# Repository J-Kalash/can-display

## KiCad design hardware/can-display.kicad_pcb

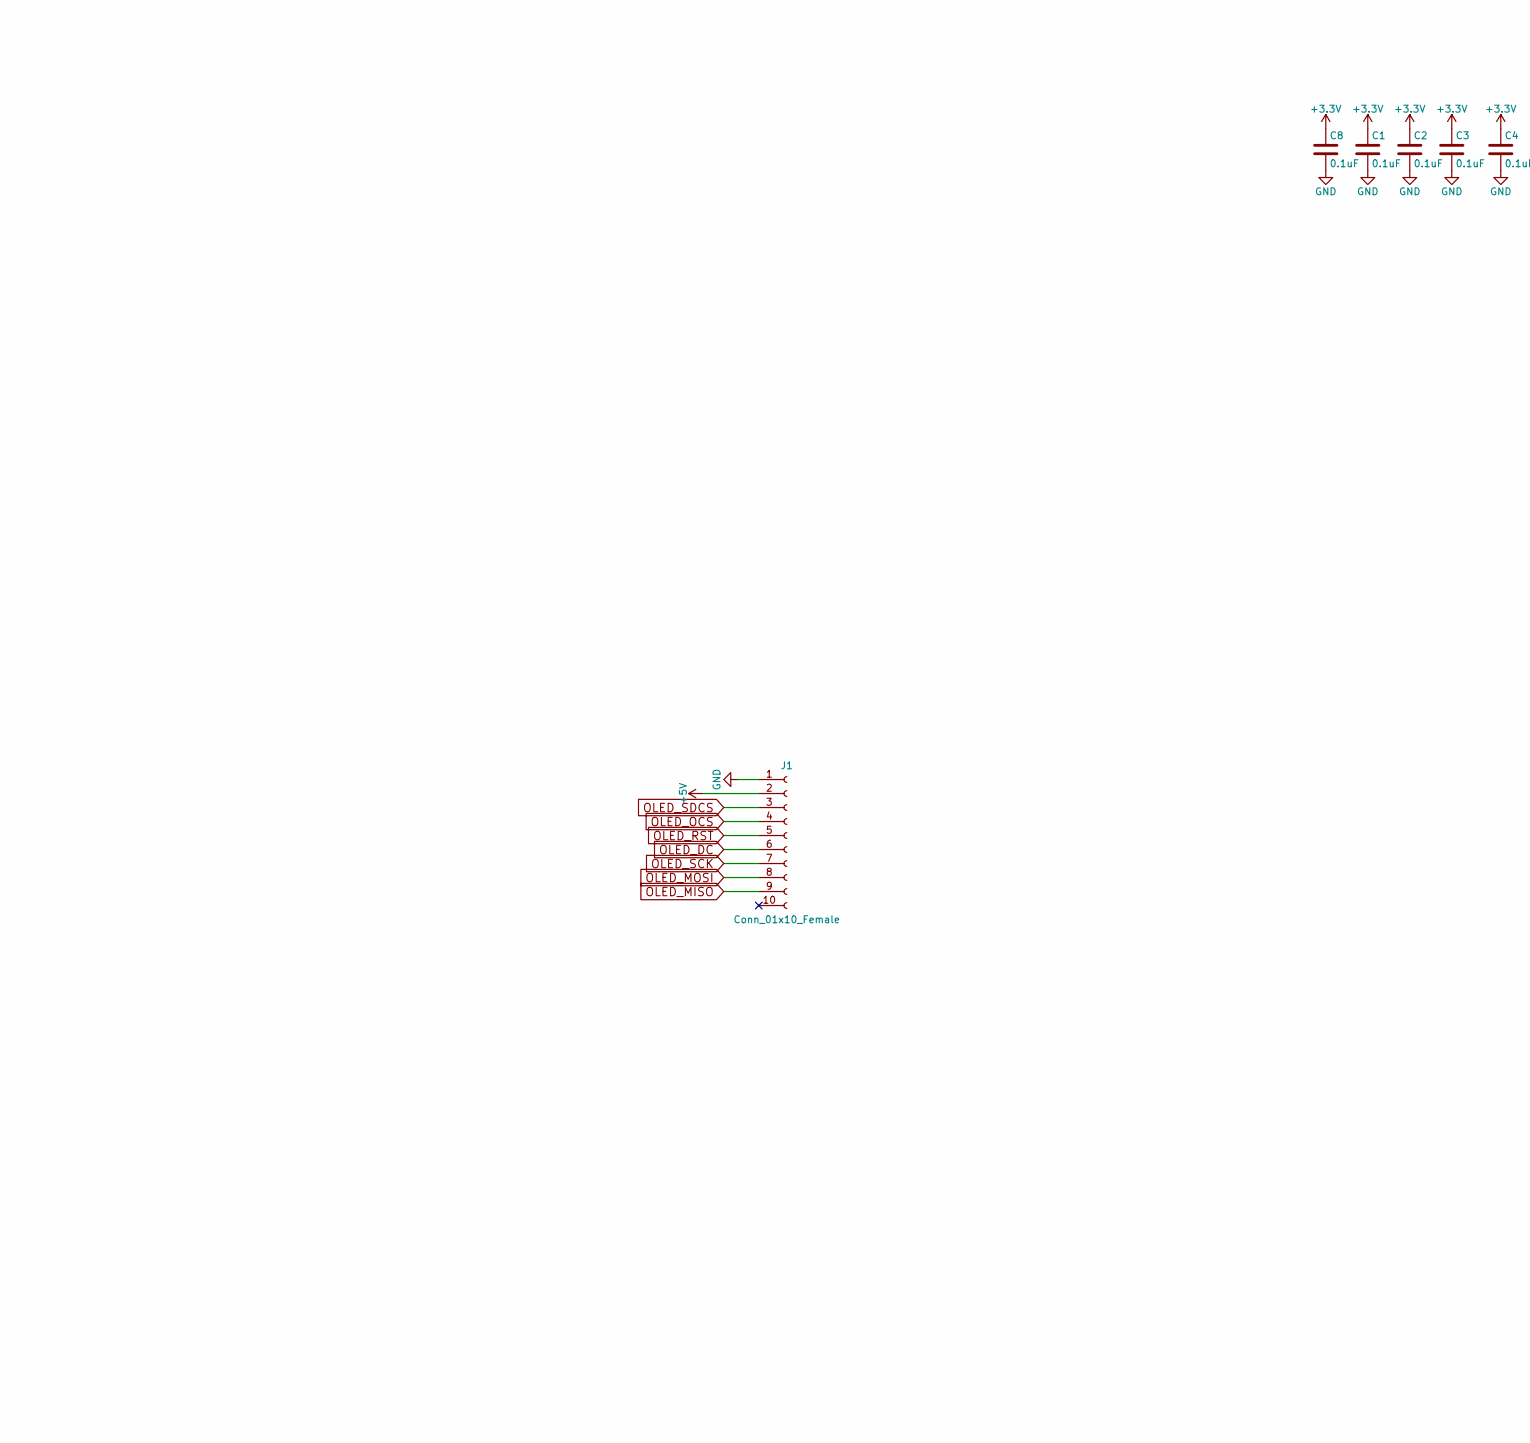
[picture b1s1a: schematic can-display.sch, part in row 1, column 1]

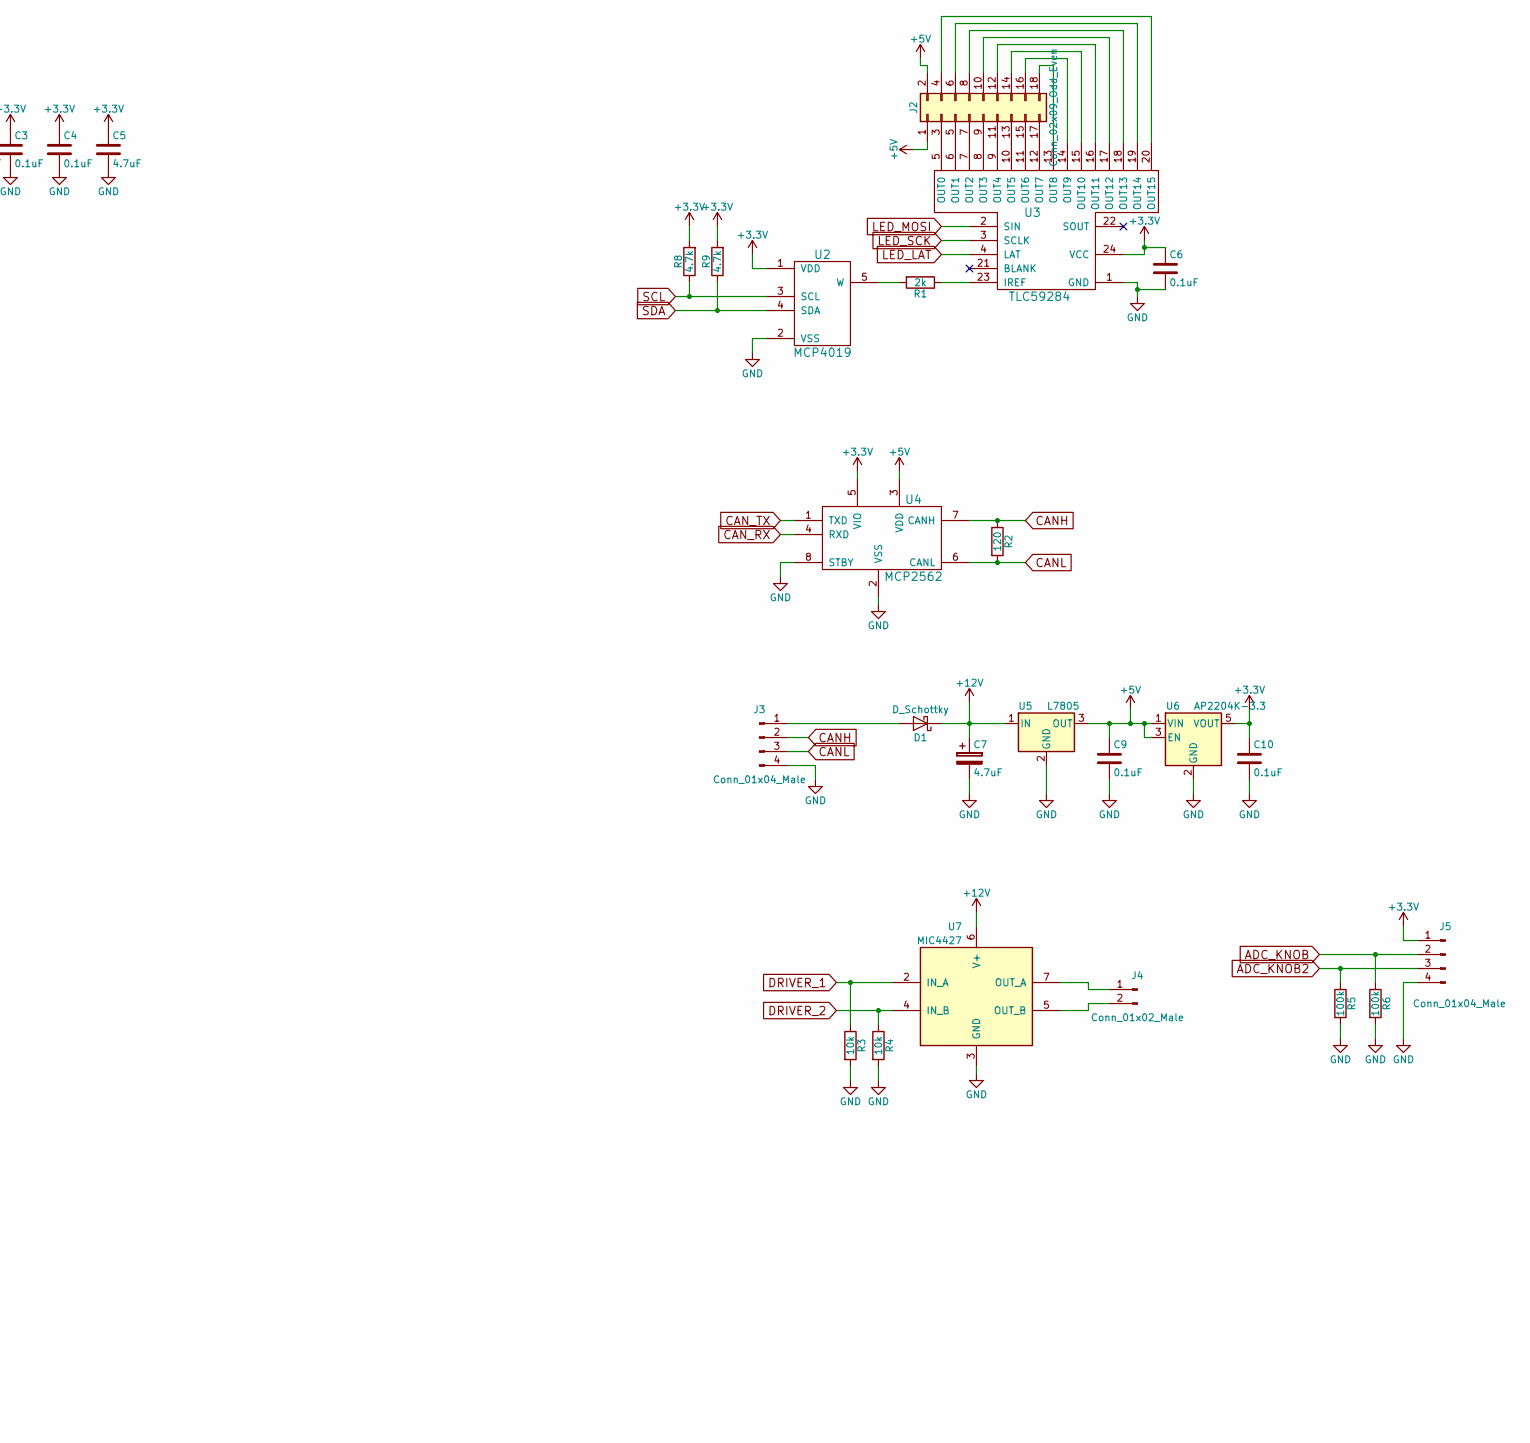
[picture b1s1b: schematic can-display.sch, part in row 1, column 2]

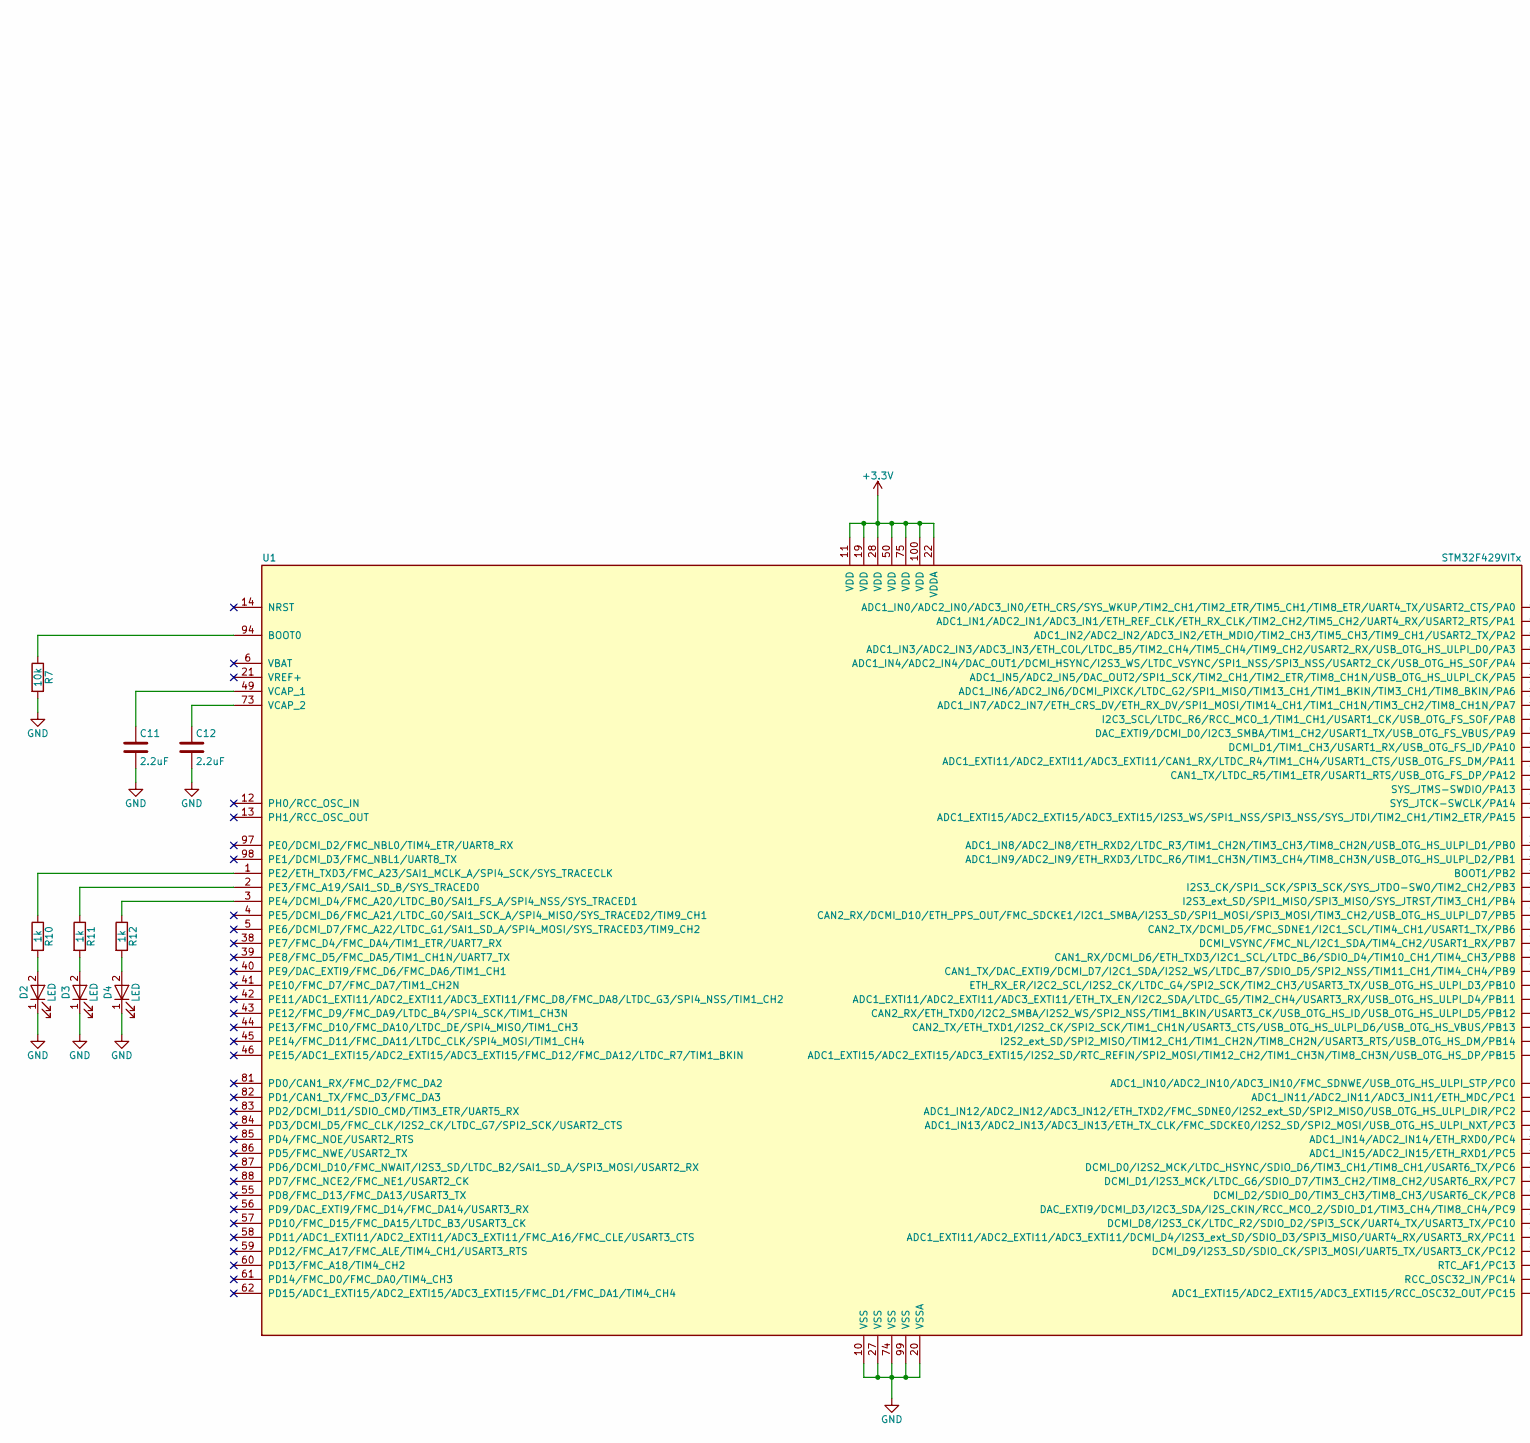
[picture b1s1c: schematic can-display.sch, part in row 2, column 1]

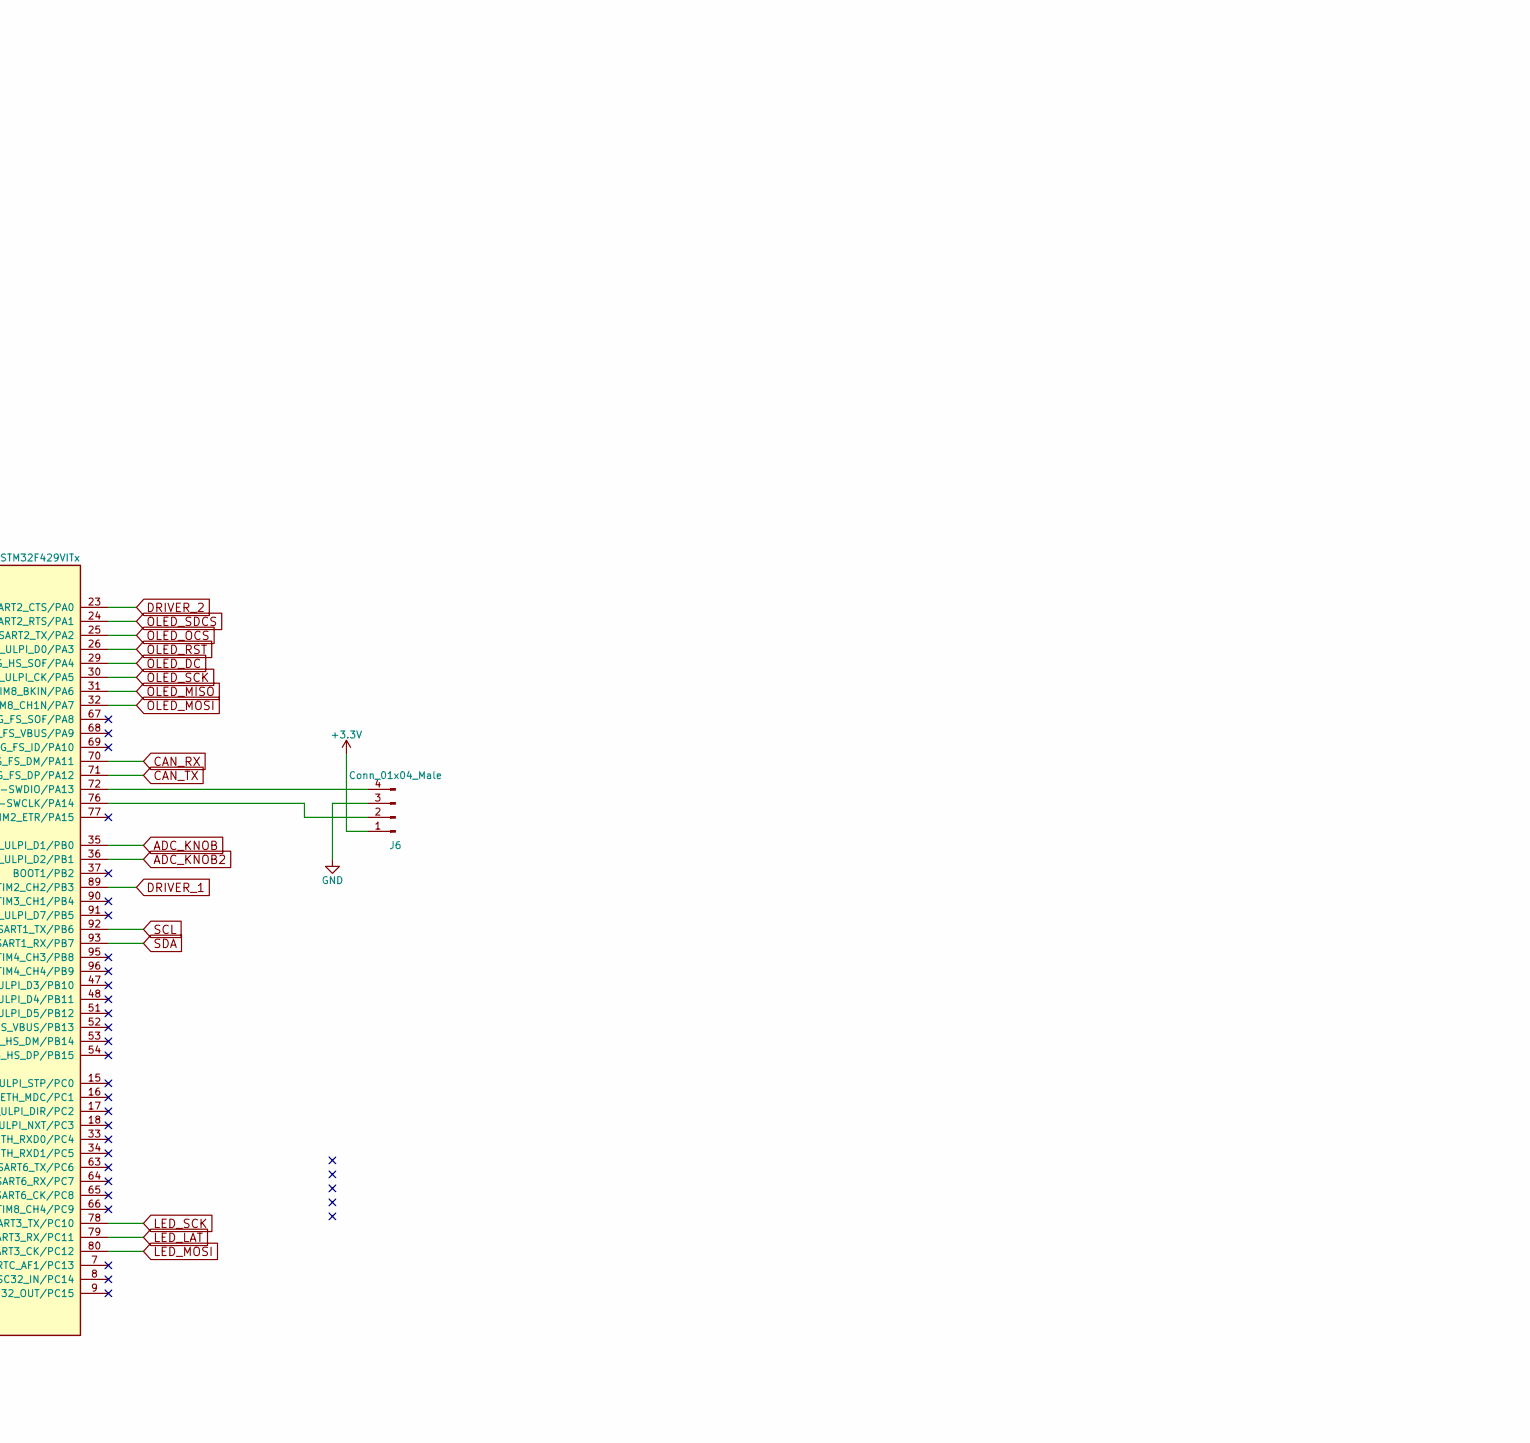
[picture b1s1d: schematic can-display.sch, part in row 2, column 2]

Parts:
C1, C2, C3, C4, C6, C8, C9, C10: 0.1uF; C_0603
C5: 4.7uF; C_0603
C7: 4.7uF; CP_Tantalum_Case-B_EIA-3528-21_Wave
C11, C12: 2.2uF; C_0603
D1: D_Schottky; D_SOD-123F
D2, D3, D4: LED; LED_0603_HandSoldering
J1: Conn_01x10_Female; Socket_Strip_Straight_1x10_Pitch2.54mm
J2: Conn_02x09_Odd_Even; Socket_Strip_Straight_2x09_Pitch2.54mm_SMD
J3, J5: Conn_01x04_Male; JST_XH_B04B-XH-A_04x2.50mm_Straight
J4: Conn_01x02_Male; JST_XH_B02B-XH-A_02x2.50mm_Straight
J6: Conn_01x04_Male; Pin_Header_Straight_1x04_Pitch2.54mm
R1: 2k; R_0603
R2: 120; R_0603
R3, R4, R7: 10k; R_0603
R5, R6: 100k; R_0603
R8, R9: 4.7k; R_0603
R10, R11, R12: 1k; R_0603
U1: STM32F429VITx; LQFP-100_14x14mm_Pitch0.5mm
U2: MCP4019; SOT-353_SC-70-5_Handsoldering
U3: TLC59284; SSOP-24_3.9x8.7mm_Pitch0.635mm
U4: MCP2562; SOIC-8_3.9x4.9mm_Pitch1.27mm
U5: L7805; TO-252-2
U6: AP2204K-3.3; SOT-23-5_HandSoldering
U7: MIC4427; SOIC-8_3.9x4.9mm_Pitch1.27mm

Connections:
+3V3: C1.1, C2.1, C3.1, C4.1, C5.1, C6.1, C8.1, C10.1, J5.1, J6.1, R8.2, R9.2, U1.11 (VDD), U1.19 (VDD), U1.22 (VDDA), U1.28 (VDD), U1.50 (VDD), U1.75 (VDD), U1.100 (VDD), U2.1 (VDD), U3.24 (VCC), U4.5 (VIO), U6.5 (VOUT)
+5V: C9.1, J1.2, J2.1, J2.2, U4.3 (VDD), U5.3 (OUT), U6.1 (VIN), U6.3 (EN)
+12V: C7.1, D1.1 (K), U5.1 (IN), U7.6 (V+)
ADC_KNOB: J5.2, R6.1, U1.35 (ADC1_IN8/ADC2_IN8/ETH_RXD2/LTDC_R3/TIM1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)
ADC_KNOB2: J5.3, R5.1, U1.36 (ADC1_IN9/ADC2_IN9/ETH_RXD3/LTDC_R6/TIM1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)
CANH: J3.2, R2.1, U4.7 (CANH)
CANL: J3.3, R2.2, U4.6 (CANL)
CAN_RX: U1.70 (ADC1_EXTI11/ADC2_EXTI11/ADC3_EXTI11/CAN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), U4.4 (RXD)
CAN_TX: U1.71 (CAN1_TX/LTDC_R5/TIM1_ETR/USART1_RTS/USB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), U4.1 (TXD)
DRIVER_1: R3.1, U1.89 (I2S3_CK/SPI1_SCK/SPI3_SCK/SYS_JTDO-SWO/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), U7.2 (IN_A)
DRIVER_2: R4.1, U1.23 (ADC1_IN0/ADC2_IN0/ADC3_IN0/ETH_CRS/SYS_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), U7.4 (IN_B)
GND: C1.2, C2.2, C3.2, C4.2, C5.2, C6.2, C7.2, C8.2, C9.2, C10.2, C11.2, C12.2, D2.1 (K), D3.1 (K), D4.1 (K), J1.1, J3.4, J5.4, J6.3, R3.2, R4.2, R5.2, R6.2, R7.2, U1.10 (VSS), U1.20 (VSSA), U1.27 (VSS), U1.74 (VSS), U1.99 (VSS), U2.2 (VSS), U3.1 (GND), U4.2 (VSS), U4.8 (STBY), U5.2 (GND), U6.2 (GND), U7.3 (GND)
LED_LAT: U1.79 (ADC1_EXTI11/ADC2_EXTI11/ADC3_EXTI11/DCM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), U3.4 (LAT)
LED_MOSI: U1.80 (DCMI_D9/I2S3_SD/SDIO_CK/SPI3_MOSI/UART5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), U3.2 (SIN)
LED_SCK: U1.78 (DCMI_D8/I2S3_CK/LTDC_R2/SDIO_D2/SPI3_SC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), U3.3 (SCLK)
unnamed: C11.1, U1.49 (VCAP_1)
unnamed: C12.1, U1.73 (VCAP_2)
unnamed: D1.2 (A), J3.1
unnamed: D2.2 (A), R10.2
unnamed: D3.2 (A), R11.2
unnamed: D4.2 (A), R12.2
unnamed: J2.3, U3.5 (OUT0)
unnamed: J2.4, U3.20 (OUT15)
unnamed: J2.5, U3.6 (OUT1)
unnamed: J2.6, U3.19 (OUT14)
unnamed: J2.7, U3.7 (OUT2)
unnamed: J2.8, U3.18 (OUT13)
unnamed: J2.9, U3.8 (OUT3)
unnamed: J2.10, U3.17 (OUT12)
unnamed: J2.11, U3.9 (OUT4)
unnamed: J2.12, U3.16 (OUT11)
unnamed: J2.13, U3.10 (OUT5)
unnamed: J2.14, U3.15 (OUT10)
unnamed: J2.15, U3.11 (OUT6)
unnamed: J2.16, U3.14 (OUT9)
unnamed: J2.17, U3.12 (OUT7)
unnamed: J2.18, U3.13 (OUT8)
unnamed: J4.1, U7.7 (OUT_A)
unnamed: J4.2, U7.5 (OUT_B)
unnamed: J6.2, U1.76 (SYS_JTCK-SWCLK/PA14)
unnamed: J6.4, U1.72 (SYS_JTMS-SWDIO/PA13)
unnamed: R1.1, U3.23 (IREF)
unnamed: R1.2, U2.5 (W)
unnamed: R7.1, U1.94 (BOOT0)
unnamed: R10.1, U1.1 (PE2/ETH_TXD3/FMC_A23/SAI1_MCLK_A/SPI4_S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)
unnamed: R11.1, U1.2 (PE3/FMC_A19/SAI1_SD_B/SYS_TRACED0)
unnamed: R12.1, U1.3 (PE4/DCMI_D4/FMC_A20/LTDC_B0/SAI1_FS_A/S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)
OLED_DC: J1.6, U1.29 (ADC1_IN4/ADC2_IN4/DAC_OUT1/DCMI_HSYNC/I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)
OLED_MISO: J1.9, U1.31 (ADC1_IN6/ADC2_IN6/DCMI_PIXCK/LTDC_G2/SP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)
OLED_MOSI: J1.8, U1.32 (ADC1_IN7/ADC2_IN7/ETH_CRS_DV/ETH_RX_DV/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)
OLED_OCS: J1.4, U1.25 (ADC1_IN2/ADC2_IN2/ADC3_IN2/ETH_MDIO/TIM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)
OLED_RST: J1.5, U1.26 (ADC1_IN3/ADC2_IN3/ADC3_IN3/ETH_COL/LTDC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)
OLED_SCK: J1.7, U1.30 (ADC1_IN5/ADC2_IN5/DAC_OUT2/SPI1_SCK/TIM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)
OLED_SDCS: J1.3, U1.24 (ADC1_IN1/ADC2_IN1/ADC3_IN1/ETH_REF_CLK/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)
SCL: R8.1, U1.92 (CAN2_TX/DCMI_D5/FMC_SDNE1/I2C1_SCL/TIM4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), U2.3 (SCL)
SDA: R9.1, U1.93 (DCMI_VSYNC/FMC_NL/I2C1_SDA/TIM4_CH2/USA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), U2.4 (SDA)

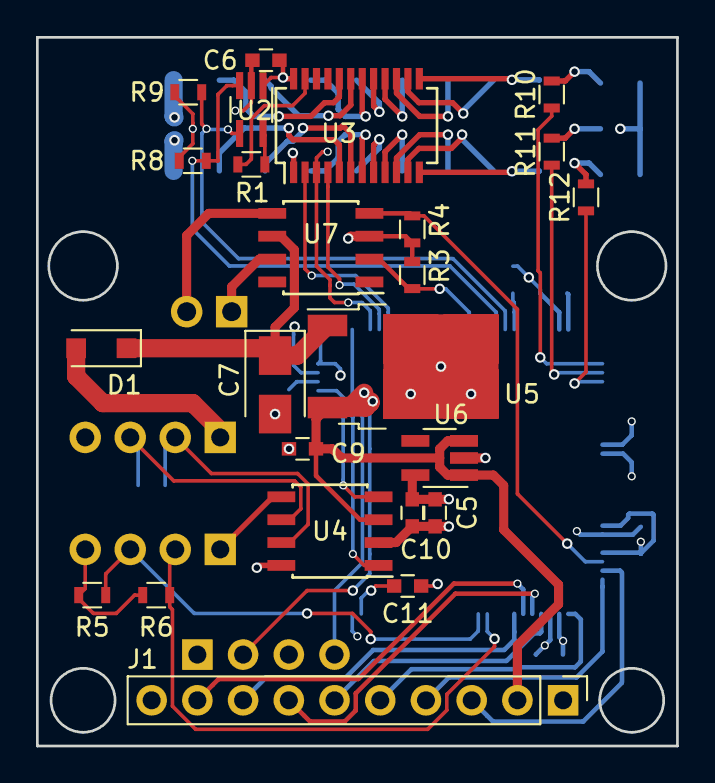
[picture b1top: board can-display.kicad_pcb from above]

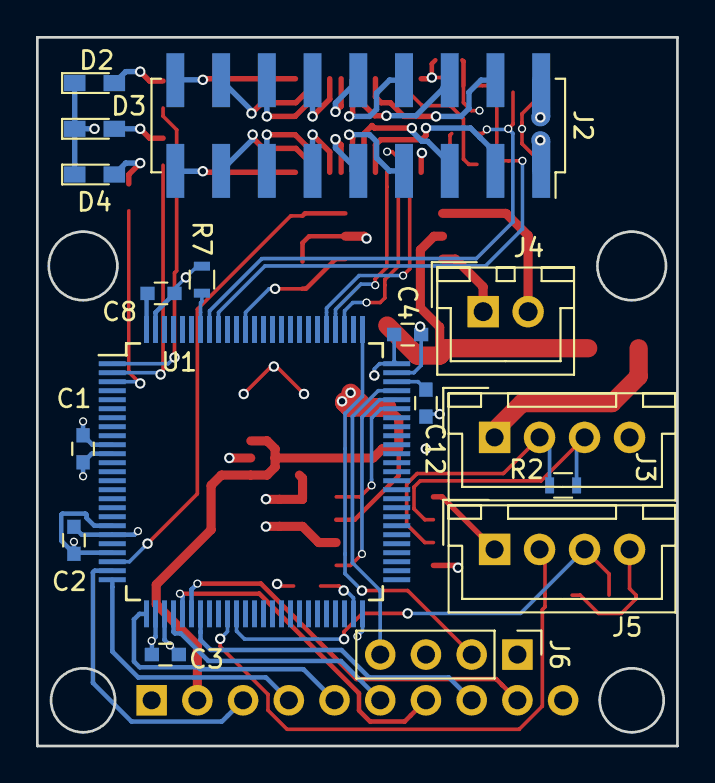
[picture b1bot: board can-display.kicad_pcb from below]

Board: 4 copper layers, 35.6 x 39.4 mm, 41 parts (17 on the bottom side), 56 nets.

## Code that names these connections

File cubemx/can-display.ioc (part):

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Mcu.Name=STM32F072C(8-B)Tx
Mcu.Package=LQFP48
Mcu.UserName=STM32F072C8Tx
PA1.Signal=GPIO_Output
PA11.Mode=Master
PA11.Signal=CAN_RX
PA12.Mode=Master
PA12.Signal=CAN_TX
PA2.Signal=GPIO_Output
PA3.Signal=GPIO_Output
PA4.Signal=GPIO_Output
PA5.Mode=Full_Duplex_Master
PA5.Signal=SPI1_SCK
PA6.Mode=Full_Duplex_Master
PA6.Signal=SPI1_MISO
PB0.Mode=IN8
PB0.Signal=ADC_IN8
PB1.Mode=IN9
PB1.Signal=ADC_IN9
PB12.Signal=GPIO_Output
PB13.Mode=TX_Only_Simplex_Unidirect_Master
PB13.Signal=SPI2_SCK
PB15.Mode=TX_Only_Simplex_Unidirect_Master
PB15.Signal=SPI2_MOSI
PB3.Signal=S_TIM2_CH2
PB4.Signal=S_TIM3_CH1
PB5.Mode=Full_Duplex_Master
PB5.Signal=SPI1_MOSI
PB6.Mode=I2C
PB6.Signal=I2C1_SCL
PB7.Mode=I2C
PB7.Signal=I2C1_SDA
RCC.SYSCLKFreq_VALUE=48000000
RCC.SYSCLKSource=RCC_SYSCLKSOURCE_HSI48

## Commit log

2018-04-01 gitignore
2018-04-01 gitignore again
2018-04-01 more gitignore
2018-04-01 Add project
2018-04-01 even more gitignore
2018-04-01 Switch to other CAN port, and fix bit timing
2018-04-06 Split out gitignore by firm/hardware
2018-04-06 add board
2018-04-06 add cubemx f0
2018-04-06 schematic and route f4
2018-04-06 add vcap_1
2018-04-06 Switch to F336RET6
2018-04-06 Adjust text on board
2018-04-06 Add i2c resistors
2018-04-17 switch to f429
2018-05-01 add lcd, render, fonts
2018-05-01 calibri, comic sans, counter strike 30
2018-05-01 move stack to core coupled ram
2018-05-01 fix multi font, copy to ram3
2018-05-01 switch to 16-bit SPI for display updates
2018-05-02 change pinning
2018-05-02 fix CAN
2018-05-02 fix CPU clock
2018-05-03 focus testing
2018-05-03 fix spi bit rate, clean up
2018-05-03 implement steering angle, wheel speed
2018-05-03 change font
2018-05-03 board almost final
